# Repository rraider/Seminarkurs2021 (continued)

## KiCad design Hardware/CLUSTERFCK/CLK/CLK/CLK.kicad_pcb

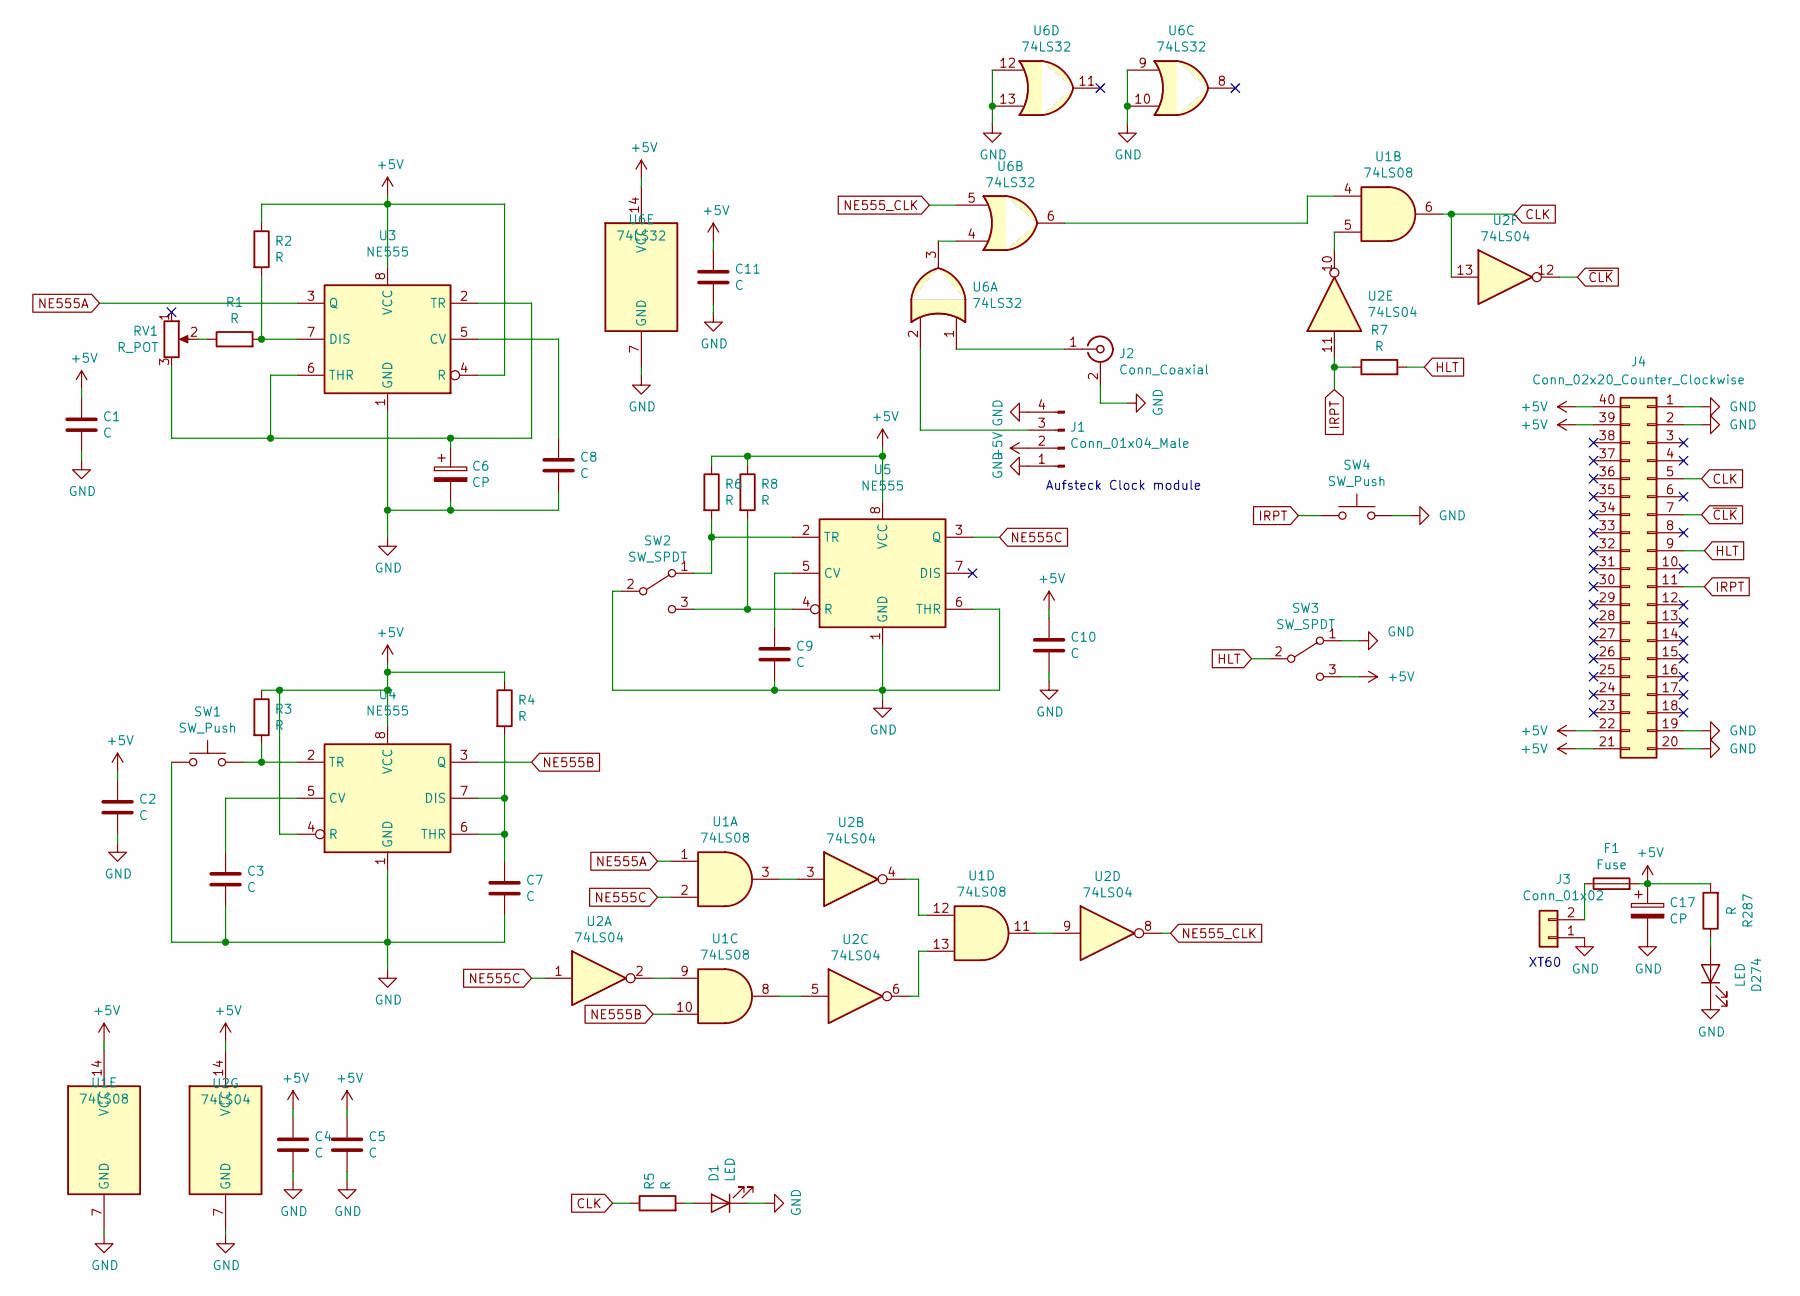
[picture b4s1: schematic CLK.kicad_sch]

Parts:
C1, C2, C3, C4, C5, C7, C8, C9, C10, C11: C; C_0805_2012Metric_Pad1.15x1.40mm_HandSolder
C6, C17: CP; C_0805_2012Metric_Pad1.15x1.40mm_HandSolder
D1, D274: LED; LED_D5.0mm
F1: Fuse; Fuseholder_Cylinder-5x20mm_Stelvio-Kontek_PTF78_Horizontal_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
J1: Conn_01x04_Male; PinHeader_1x04_P2.54mm_Vertical
J2: Conn_Coaxial; SMA_Amphenol_901-144_Vertical
J3: Conn_01x02; AMASS_XT30U-F_1x02_P5.0mm_Vertical
J4: Conn_02x20_Counter_Clockwise; PinSocket_2x20_P2.54mm_Horizontal
R1, R2, R3, R4, R5, R6, R7, R8, R287: R; R_0805_2012Metric_Pad1.15x1.40mm_HandSolder
RV1: R_POT; Potentiometer_ACP_CA6-H2,5_Horizontal
SW1, SW4: SW_Push; Push_E-Switch_KS01Q01
SW2, SW3: SW_SPDT; SW_CuK_JS202011CQN_DPDT_Straight
U1: 74LS08; SOIC-14_3.9x8.7mm_P1.27mm
U2: 74LS04; SOIC-14_3.9x8.7mm_P1.27mm
U3, U4, U5: NE555; DIP-8_W10.16mm
U6: 74LS32; SOIC-14_3.9x8.7mm_P1.27mm

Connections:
+5V: C1.1, C2.1, C4.1, C5.1, C10.1, C11.1, C17.1, F1.2, J1.2, J4.21, J4.22, J4.39, J4.40, R2.1, R3.1, R4.1, R6.1, R8.1, R287.2, SW3.3 (C), U1.14 (VCC), U2.14 (VCC), U3.4 (R), U3.8 (VCC), U4.4 (R), U4.8 (VCC), U5.8 (VCC), U6.14 (VCC)
CLK: J4.5, R5.1, U1.6, U2.13
GND: C1.2, C2.2, C3.2, C4.2, C5.2, C6.2, C7.2, C8.2, C9.2, C10.2, C11.2, C17.2, D1.1 (K), D274.1 (K), J1.1, J1.4, J2.2 (Ext), J3.1, J4.1, J4.2, J4.19, J4.20, SW1.1, SW2.2 (B), SW3.1 (A), SW4.2, U1.7 (GND), U2.7 (GND), U3.1 (GND), U4.1 (GND), U5.1 (GND), U5.6 (THR), U6.7 (GND), U6.9, U6.10, U6.12, U6.13
HLT: J4.9, R7.2, SW3.2 (B)
IRPT: J4.11, R7.1, SW4.1, U2.11
NE555A: U1.1, U3.3 (Q)
NE555B: U1.10, U4.3 (Q)
NE555C: U1.2, U2.1, U5.3 (Q)
NE555_CLK: U2.8, U6.5
unnamed: C3.1, U4.5 (CV)
unnamed: C6.1, RV1.3, U3.2 (TR), U3.6 (THR)
unnamed: C7.1, R4.2, U4.6 (THR), U4.7 (DIS)
unnamed: C8.1, U3.5 (CV)
unnamed: C9.1, U5.5 (CV)
unnamed: D1.2 (A), R5.2
unnamed: D274.2 (A), R287.1
unnamed: F1.1, J3.2
unnamed: J1.3, U6.2
unnamed: J2.1 (In), U6.1
unnamed: R1.1, RV1.2
unnamed: R1.2, R2.2, U3.7 (DIS)
unnamed: R3.2, SW1.2, U4.2 (TR)
unnamed: R6.2, SW2.1 (A), U5.2 (TR)
unnamed: R8.2, SW2.3 (C), U5.4 (R)
unnamed: U1.3, U2.3
unnamed: U1.4, U6.6
unnamed: U1.5, U2.10
unnamed: U1.8, U2.5
unnamed: U1.9, U2.2
unnamed: U1.11, U2.9
unnamed: U1.12, U2.4
unnamed: U1.13, U2.6
unnamed: U6.3, U6.4
no_connect_35: J4.10
no_connect_36: J4.12
no_connect_37: J4.13
no_connect_38: J4.14
no_connect_39: J4.15
no_connect_40: J4.16
no_connect_41: J4.17
no_connect_42: J4.18
no_connect_43: J4.23
no_connect_44: J4.24
no_connect_45: J4.25
no_connect_46: J4.26
no_connect_47: J4.27
no_connect_48: J4.28
no_connect_49: J4.29
no_connect_50: J4.3
no_connect_51: J4.30
no_connect_52: J4.31
no_connect_53: J4.32
no_connect_54: J4.33
no_connect_55: J4.34
no_connect_56: J4.35
no_connect_57: J4.36
no_connect_58: J4.37
no_connect_59: J4.38
no_connect_60: J4.4
no_connect_61: J4.6
no_connect_62: J4.8
no_connect_63: RV1.1
no_connect_64: U5.7 (DIS)
no_connect_65: U6.11
no_connect_66: U6.8
~CLK: J4.7, U2.12

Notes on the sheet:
Aufsteck Clock module
XT60

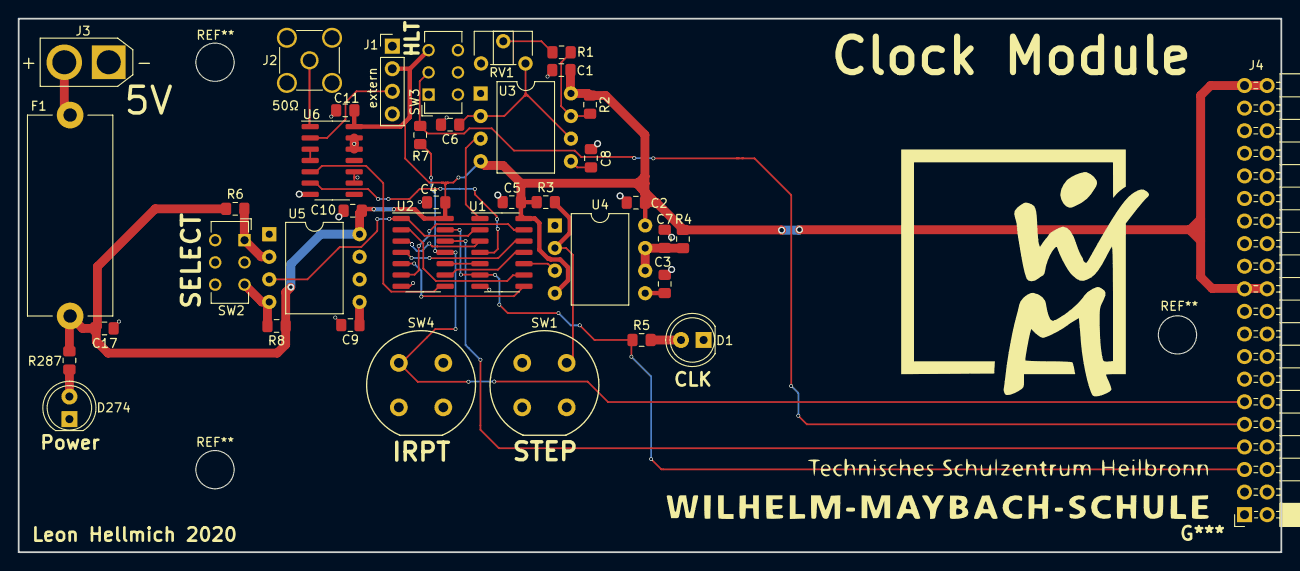
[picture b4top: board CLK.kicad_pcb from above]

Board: 2 copper layers, 142.0 x 60.0 mm, 39 parts (0 on the bottom side), 34 nets.

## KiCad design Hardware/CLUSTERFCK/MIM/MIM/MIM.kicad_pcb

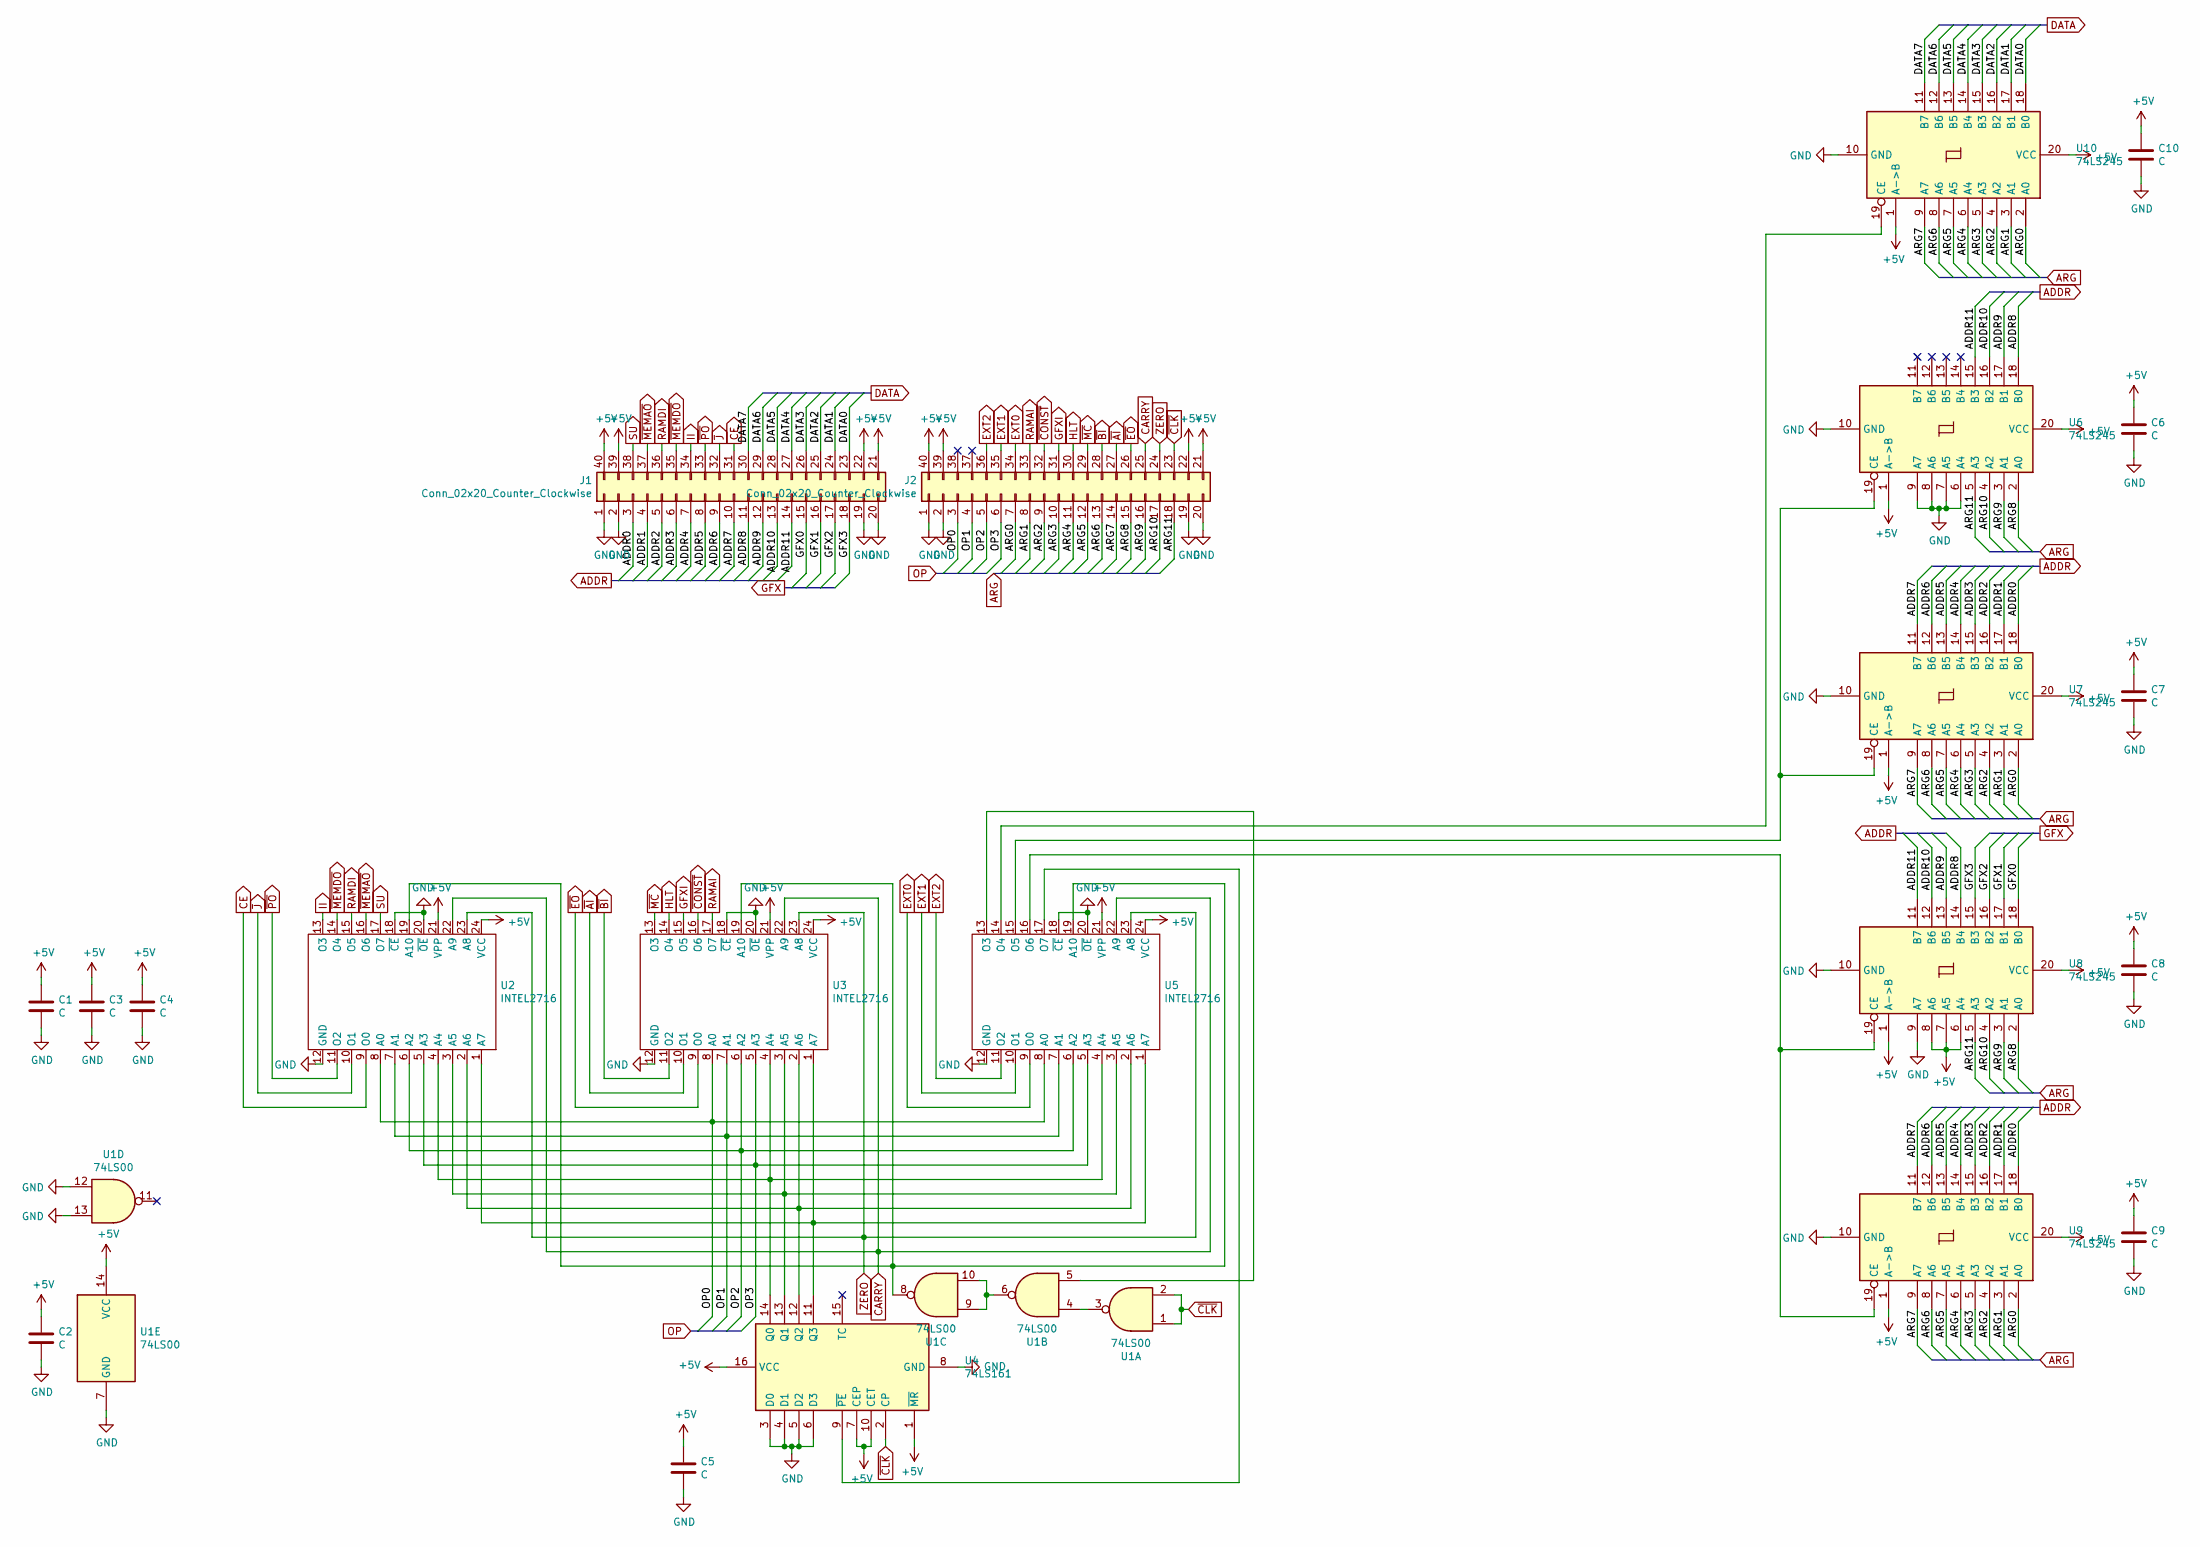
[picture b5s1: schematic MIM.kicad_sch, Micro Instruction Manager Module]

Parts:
C1, C2, C3, C4, C5, C6, C7, C8, C9, C10: C; C_0805_2012Metric_Pad1.15x1.40mm_HandSolder
J1, J2: Conn_02x20_Counter_Clockwise; PinSocket_2x20_P2.54mm_Horizontal
U1: 74LS00; SOIC-14_3.9x8.7mm_P1.27mm
U2, U3, U5: INTEL2716; DIP-24_W15.24mm_Socket_LongPads
U4: 74LS161; SOIC-16_3.9x9.9mm_P1.27mm
U6, U7, U8, U9, U10: 74LS245; SOIC-20W_7.5x12.8mm_P1.27mm

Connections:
+5V: C1.1, C2.1, C3.1, C4.1, C5.1, C6.1, C7.1, C8.1, C9.1, C10.1, J1.21, J1.22, J1.39, J1.40, J2.21, J2.22, J2.39, J2.40, U1.14 (VCC), U2.21 (VPP), U2.24 (VCC), U3.21 (VPP), U3.24 (VCC), U4.1 (~MR), U4.7 (CEP), U4.10 (CET), U4.16 (VCC), U5.21 (VPP), U5.24 (VCC), U6.1 (A->B), U6.20 (VCC), U7.1 (A->B), U7.20 (VCC), U8.1 (A->B), U8.6 (A4), U8.7 (A5), U8.8 (A6), U8.20 (VCC), U9.1 (A->B), U9.20 (VCC), U10.1 (A->B), U10.20 (VCC)
/ADDR0: J1.3, U7.18 (B0), U9.18 (B0)
/ADDR1: J1.4, U7.17 (B1), U9.17 (B1)
/ADDR2: J1.5, U7.16 (B2), U9.16 (B2)
/ADDR3: J1.6, U7.15 (B3), U9.15 (B3)
/ADDR4: J1.7, U7.14 (B4), U9.14 (B4)
/ADDR5: J1.8, U7.13 (B5), U9.13 (B5)
/ADDR6: J1.9, U7.12 (B6), U9.12 (B6)
/ADDR7: J1.10, U7.11 (B7), U9.11 (B7)
/ADDR8: J1.11, U6.18 (B0), U8.14 (B4)
/ADDR9: J1.12, U6.17 (B1), U8.13 (B5)
/ADDR10: J1.13, U6.16 (B2), U8.12 (B6)
/ADDR11: J1.14, U6.15 (B3), U8.11 (B7)
/ARG0: J2.7, U7.2 (A0), U9.2 (A0), U10.2 (A0)
/ARG1: J2.8, U7.3 (A1), U9.3 (A1), U10.3 (A1)
/ARG2: J2.9, U7.4 (A2), U9.4 (A2), U10.4 (A2)
/ARG3: J2.10, U7.5 (A3), U9.5 (A3), U10.5 (A3)
/ARG4: J2.11, U7.6 (A4), U9.6 (A4), U10.6 (A4)
/ARG5: J2.12, U7.7 (A5), U9.7 (A5), U10.7 (A5)
/ARG6: J2.13, U7.8 (A6), U9.8 (A6), U10.8 (A6)
/ARG7: J2.14, U7.9 (A7), U9.9 (A7), U10.9 (A7)
/ARG8: J2.15, U6.2 (A0), U8.2 (A0)
/ARG9: J2.16, U6.3 (A1), U8.3 (A1)
/ARG10: J2.17, U6.4 (A2), U8.4 (A2)
/ARG11: J2.18, U6.5 (A3), U8.5 (A3)
/DATA0: J1.23, U10.18 (B0)
/DATA1: J1.24, U10.17 (B1)
/DATA2: J1.25, U10.16 (B2)
/DATA3: J1.26, U10.15 (B3)
/DATA4: J1.27, U10.14 (B4)
/DATA5: J1.28, U10.13 (B5)
/DATA6: J1.29, U10.12 (B6)
/DATA7: J1.30, U10.11 (B7)
/GFX0: J1.15, U8.18 (B0)
/GFX1: J1.16, U8.17 (B1)
/GFX2: J1.17, U8.16 (B2)
/GFX3: J1.18, U8.15 (B3)
/OP0: J2.3, U2.8 (A0), U3.8 (A0), U5.8 (A0)
/OP1: J2.4, U2.7 (A1), U3.7 (A1), U5.7 (A1)
/OP2: J2.5, U2.6 (A2), U3.6 (A2), U5.6 (A2)
/OP3: J2.6, U2.5 (A3), U3.5 (A3), U5.5 (A3)
AI: J2.27, U3.10 (O1)
BI: J2.28, U3.11 (O2)
CARRY: J2.25, U2.22 (A9), U3.22 (A9), U5.22 (A9)
CE: J1.31, U2.9 (O0)
CONST: J2.32, U3.16 (O6)
EO: J2.26, U3.9 (O0)
EXT0: J2.34, U5.9 (O0)
EXT1: J2.35, U5.10 (O1)
EXT2: J2.36, U5.11 (O2)
GFXI: J2.31, U3.15 (O5)
GND: C1.2, C2.2, C3.2, C4.2, C5.2, C6.2, C7.2, C8.2, C9.2, C10.2, J1.1, J1.2, J1.19, J1.20, J2.1, J2.2, J2.19, J2.20, U1.7 (GND), U1.12, U1.13, U2.12 (GND), U2.18 (~CE), U2.20 (~OE), U3.12 (GND), U3.18 (~CE), U3.20 (~OE), U4.3 (D0), U4.4 (D1), U4.5 (D2), U4.6 (D3), U4.8 (GND), U5.12 (GND), U5.18 (~CE), U5.20 (~OE), U6.6 (A4), U6.7 (A5), U6.8 (A6), U6.9 (A7), U6.10 (GND), U7.10 (GND), U8.9 (A7), U8.10 (GND), U9.10 (GND), U10.10 (GND)
HLT: J2.30, U3.14 (O4)
II: J1.34, U2.13 (O3)
J: J1.32, U2.10 (O1)
MC: J2.29, U3.13 (O3)
MEMAO: J1.37, U2.16 (O6)
MEMDO: J1.35, U2.14 (O4)
unnamed: U1.3, U1.4
unnamed: U1.5, U5.13 (O3)
unnamed: U1.8, U2.19 (A10), U3.19 (A10), U5.19 (A10)
unnamed: U1.6, U1.9, U1.10
unnamed: U2.1 (A7), U3.1 (A7), U4.11 (Q3), U5.1 (A7)
unnamed: U2.2 (A6), U3.2 (A6), U4.12 (Q2), U5.2 (A6)
unnamed: U2.3 (A5), U3.3 (A5), U4.13 (Q1), U5.3 (A5)
unnamed: U2.4 (A4), U3.4 (A4), U4.14 (Q0), U5.4 (A4)
unnamed: U4.9 (~PE), U5.17 (O7)
unnamed: U5.15 (O5), U6.19 (CE), U7.19 (CE)
unnamed: U5.16 (O6), U8.19 (CE), U9.19 (CE)
unnamed: U5.14 (O4), U10.19 (CE)
PO: J1.33, U2.11 (O2)
RAMAI: J2.33, U3.17 (O7)
RAMDI: J1.36, U2.15 (O5)
SU: J1.38, U2.17 (O7)
ZERO: J2.24, U2.23 (A8), U3.23 (A8), U5.23 (A8)
~CLK: J2.23, U1.1, U1.2, U4.2 (CP)

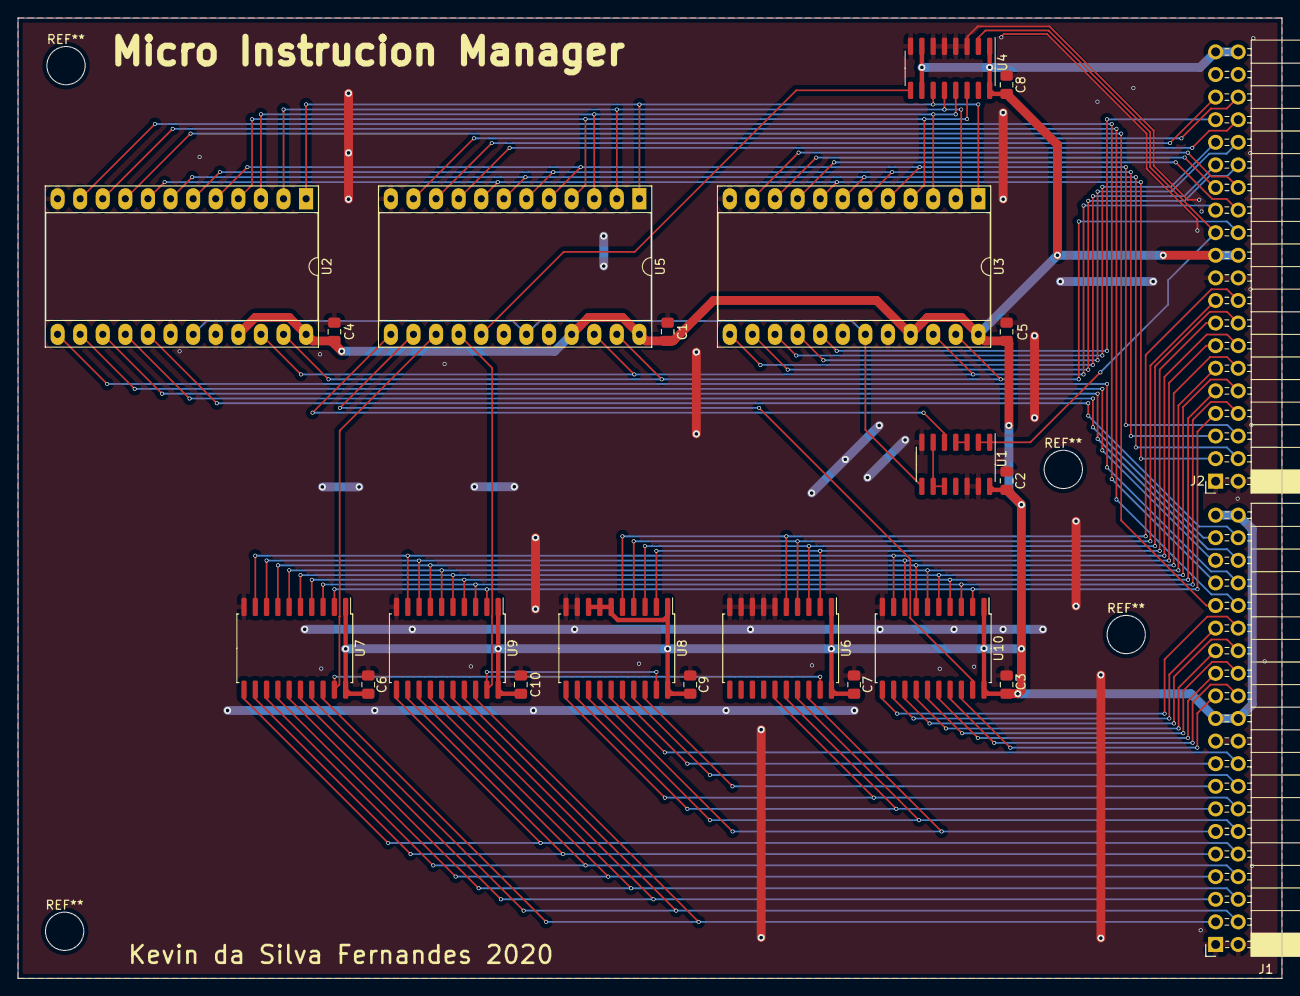
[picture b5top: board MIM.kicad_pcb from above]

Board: 2 copper layers, 142.1 x 108.0 mm, 22 parts (0 on the bottom side), 76 nets.

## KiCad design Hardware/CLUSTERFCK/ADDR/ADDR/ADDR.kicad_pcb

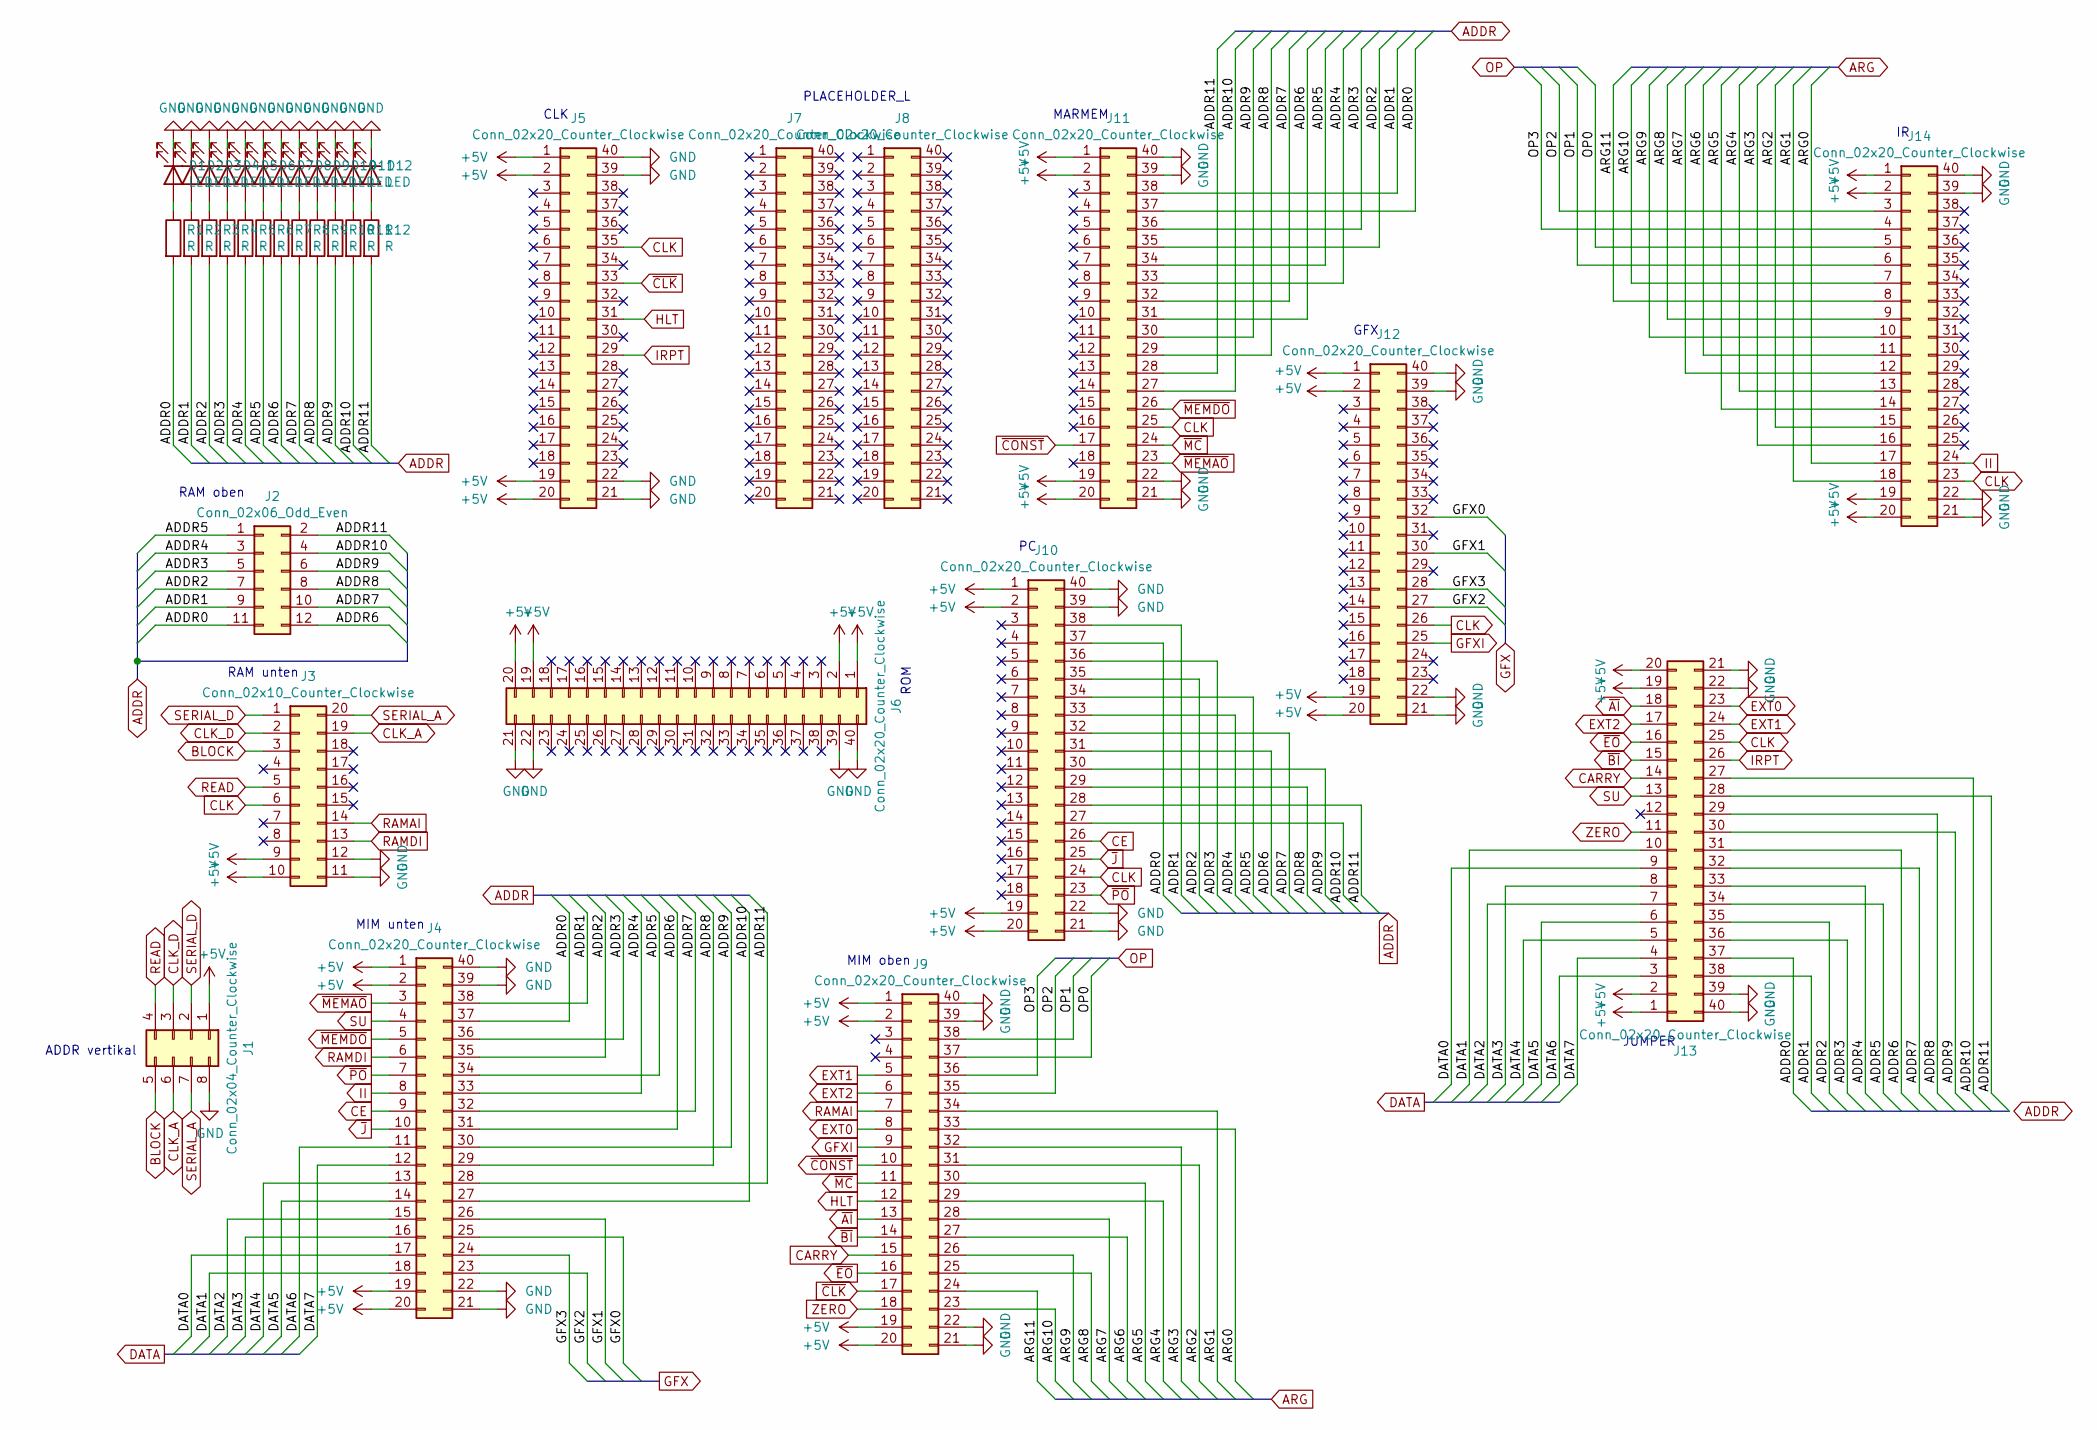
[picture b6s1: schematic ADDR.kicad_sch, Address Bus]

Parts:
D1, D2, D3, D4, D5, D6, D7, D8, D9, D10, D11, D12: LED; LED_D5.0mm
J1: Conn_02x04_Counter_Clockwise; PinHeader_2x04_P2.54mm_Vertical
J2: Conn_02x06_Odd_Even; PinHeader_2x06_P2.54mm_Horizontal
J3: Conn_02x10_Counter_Clockwise; PinHeader_2x10_P2.54mm_Horizontal
J4, J5, J6, J7, J8, J9, J10, J11, J12, J14: Conn_02x20_Counter_Clockwise; PinSocket_2x20_P2.54mm_Horizontal
J13: Conn_02x20_Counter_Clockwise; PinHeader_2x20_P2.54mm_Horizontal
R1, R2, R3, R4, R5, R6, R7, R8, R9, R10, R11, R12: R; R_0805_2012Metric_Pad1.15x1.40mm_HandSolder

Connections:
+5V: J1.1, J3.9, J3.10, J4.1, J4.2, J4.19, J4.20, J5.1, J5.2, J5.19, J5.20, J6.1, J6.2, J6.19, J6.20, J9.1, J9.2, J9.19, J9.20, J10.1, J10.2, J10.19, J10.20, J11.1, J11.2, J11.19, J11.20, J12.1, J12.2, J12.19, J12.20, J13.1, J13.2, J13.19, J13.20, J14.1, J14.2, J14.19, J14.20
/ADDR0: J2.11, J4.37, J10.37, J11.37, J13.37, R1.2
/ADDR1: J2.9, J4.38, J10.38, J11.38, J13.38, R2.2
/ADDR2: J2.7, J4.35, J10.35, J11.35, J13.35, R3.2
/ADDR3: J2.5, J4.36, J10.36, J11.36, J13.36, R4.2
/ADDR4: J2.3, J4.33, J10.33, J11.33, J13.33, R5.2
/ADDR5: J2.1, J4.34, J10.34, J11.34, J13.34, R6.2
/ADDR6: J2.12, J4.31, J10.31, J11.31, J13.31, R7.2
/ADDR7: J2.10, J4.32, J10.32, J11.32, J13.32, R8.2
/ADDR8: J2.8, J4.29, J10.29, J11.29, J13.29, R9.2
/ADDR9: J2.6, J4.30, J10.30, J11.30, J13.30, R10.2
/ADDR10: J2.4, J4.27, J10.27, J11.27, J13.27, R11.2
/ADDR11: J2.2, J4.28, J10.28, J11.28, J13.28, R12.2
/ARG0: J9.33, J14.17
/ARG1: J9.34, J14.18
/ARG2: J9.31, J14.15
/ARG3: J9.32, J14.16
/ARG4: J9.29, J14.13
/ARG5: J9.30, J14.14
/ARG6: J9.27, J14.11
/ARG7: J9.28, J14.12
/ARG8: J9.25, J14.9
/ARG9: J9.26, J14.10
/ARG10: J9.23, J14.7
/ARG11: J9.24, J14.8
/DATA0: J4.17, J13.9
/DATA1: J4.18, J13.10
/DATA2: J4.15, J13.7
/DATA3: J4.16, J13.8
/DATA4: J4.13, J13.5
/DATA5: J4.14, J13.6
/DATA6: J4.11, J13.3
/DATA7: J4.12, J13.4
/GFX0: J4.25, J12.32
/GFX1: J4.26, J12.30
/GFX2: J4.23, J12.27
/GFX3: J4.24, J12.28
/OP0: J9.37, J14.5
/OP1: J9.38, J14.6
/OP2: J9.35, J14.3
/OP3: J9.36, J14.4
BLOCK: J1.5, J3.3
CARRY: J9.15, J13.14
CE: J4.9, J10.26
CLK: J3.6, J5.35, J10.24, J11.25, J12.26, J13.25, J14.23
CLK_A: J1.6, J3.19
CLK_D: J1.3, J3.2
EXT0: J9.8, J13.23
EXT1: J9.5, J13.24
EXT2: J9.6, J13.17
GFXI: J9.9, J12.25
GND: D1.1 (K), D2.1 (K), D3.1 (K), D4.1 (K), D5.1 (K), D6.1 (K), D7.1 (K), D8.1 (K), D9.1 (K), D10.1 (K), D11.1 (K), D12.1 (K), J1.8, J3.11, J3.12, J4.21, J4.22, J4.39, J4.40, J5.21, J5.22, J5.39, J5.40, J6.21, J6.22, J6.39, J6.40, J9.21, J9.22, J9.39, J9.40, J10.21, J10.22, J10.39, J10.40, J11.21, J11.22, J11.39, J11.40, J12.21, J12.22, J12.39, J12.40, J13.21, J13.22, J13.39, J13.40, J14.21, J14.22, J14.39, J14.40
HLT: J5.31, J9.12
II: J4.8, J14.24
IRPT: J5.29, J13.26
unnamed: D6.2 (A), R6.1
unnamed: D1.2 (A), R1.1
unnamed: D2.2 (A), R2.1
unnamed: D3.2 (A), R3.1
unnamed: D4.2 (A), R4.1
unnamed: D5.2 (A), R5.1
unnamed: D7.2 (A), R7.1
unnamed: D8.2 (A), R8.1
unnamed: D9.2 (A), R9.1
unnamed: D10.2 (A), R10.1
unnamed: D11.2 (A), R11.1
unnamed: D12.2 (A), R12.1
RAMAI: J3.14, J9.7
RAMDI: J3.13, J4.6
READ: J1.4, J3.5
SERIAL_A: J1.7, J3.20
SERIAL_D: J1.2, J3.1
SU: J4.4, J13.13
ZERO: J9.18, J13.11
~AI: J9.13, J13.18
~BI: J9.14, J13.15
~CLK: J5.33, J9.17
~CONST: J9.10, J11.17
~EO: J9.16, J13.16
~J: J4.10, J10.25
~MC: J9.11, J11.24
~MEMAO: J4.3, J11.23
~MEMDO: J4.5, J11.26
~PO: J4.7, J10.23

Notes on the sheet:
ADDR vertikal
RAM oben
RAM unten
MIM unten
CLK
PLACEHOLDER_L
ROM
MIM oben
MARMEM
GFX
JUMPER

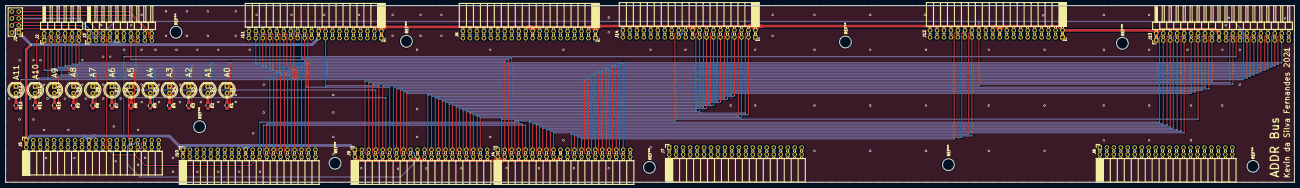
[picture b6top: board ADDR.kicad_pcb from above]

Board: 2 copper layers, 469.5 x 64.3 mm, 38 parts (0 on the bottom side), 84 nets.

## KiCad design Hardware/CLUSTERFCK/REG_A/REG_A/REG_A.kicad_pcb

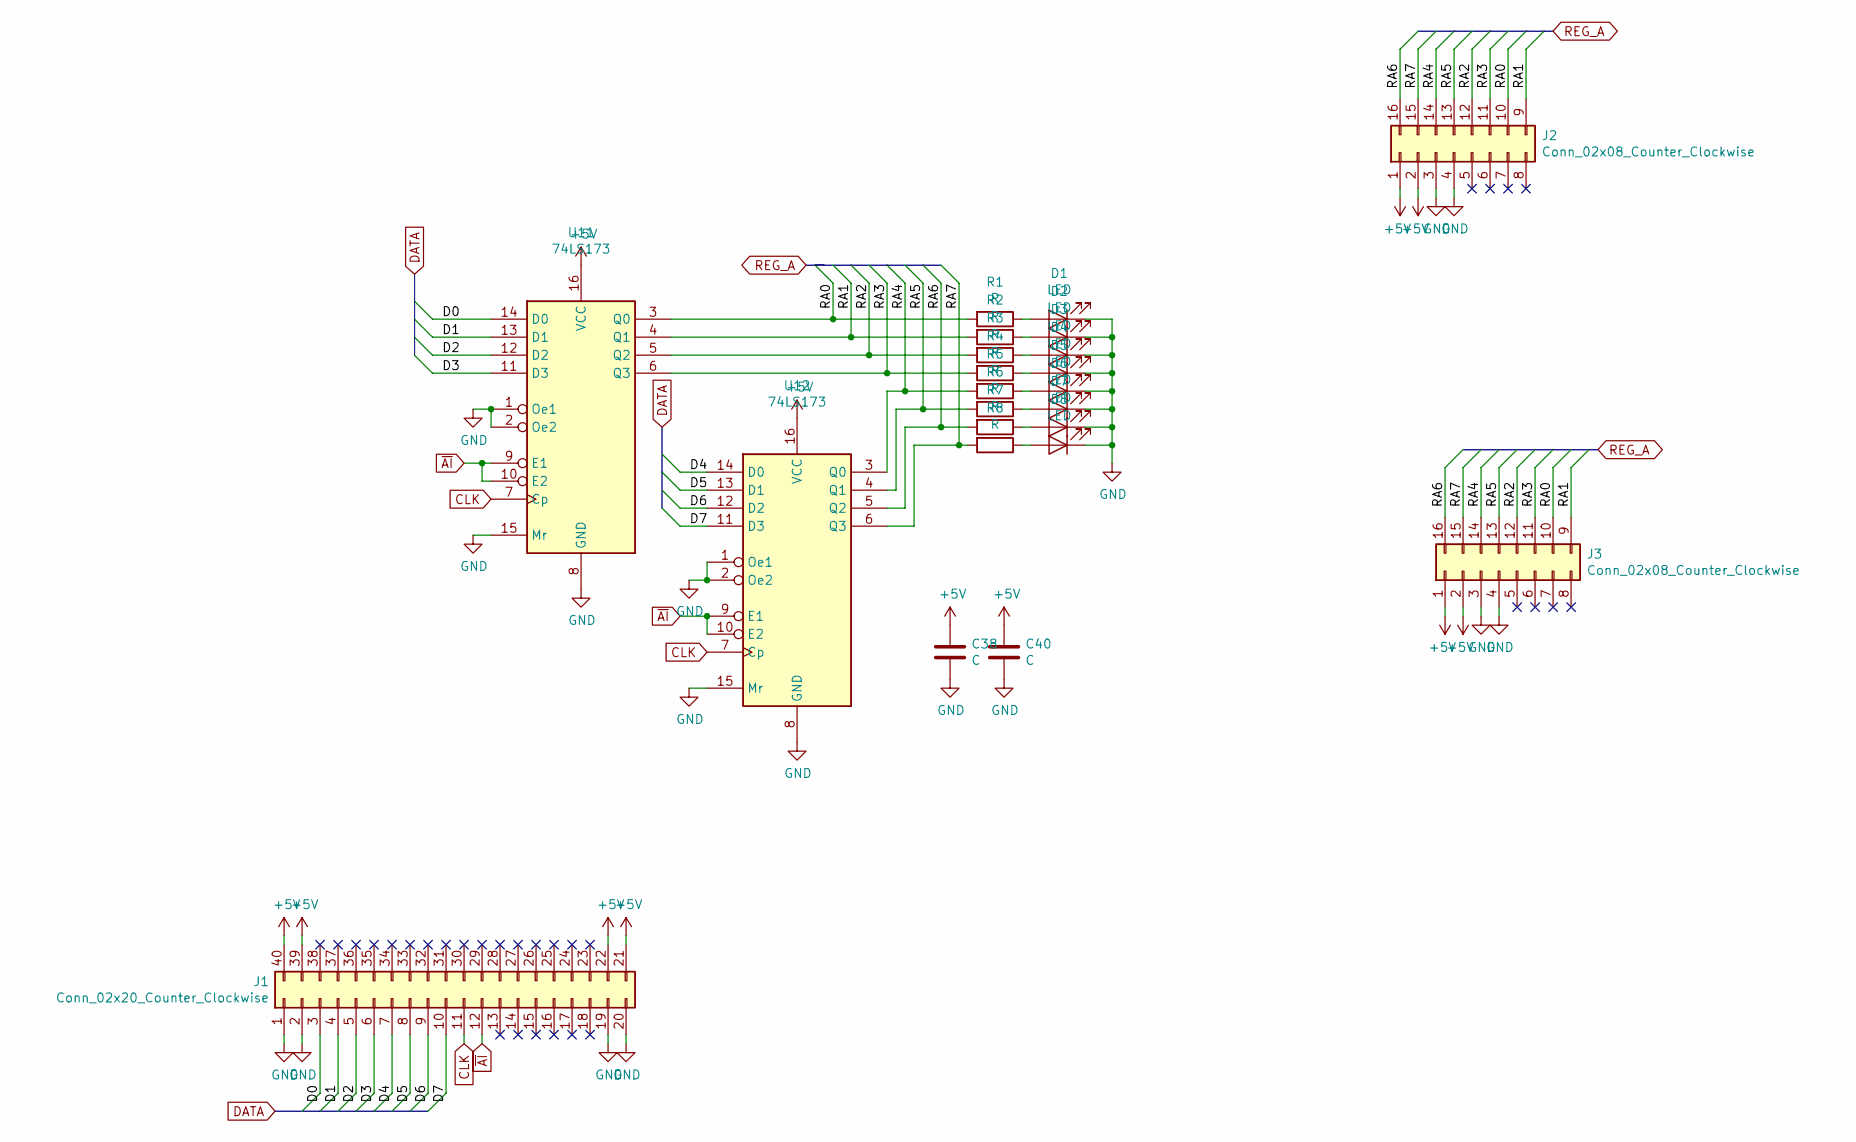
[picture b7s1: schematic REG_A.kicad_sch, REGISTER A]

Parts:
C38, C40: C; C_0805_2012Metric_Pad1.15x1.40mm_HandSolder
D1, D2, D3, D4, D5, D6, D7, D8: LED; LED_D5.0mm
J1: Conn_02x20_Counter_Clockwise; PinHeader_2x20_P2.54mm_Horizontal
J2, J3: Conn_02x08_Counter_Clockwise; PinHeader_2x08_P2.54mm_Horizontal
R1, R2, R3, R4, R5, R6, R7, R8: R; R_0805_2012Metric_Pad1.15x1.40mm_HandSolder
U11, U12: 74LS173; SOIC-16W_7.5x10.3mm_P1.27mm

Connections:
+5V: C38.1, C40.1, J1.21, J1.22, J1.39, J1.40, J2.1, J2.2, J3.1, J3.2, U11.16 (VCC), U12.16 (VCC)
/D0: J1.3, U11.14 (D0)
/D1: J1.4, U11.13 (D1)
/D2: J1.5, U11.12 (D2)
/D3: J1.6, U11.11 (D3)
/D4: J1.7, U12.14 (D0)
/D5: J1.8, U12.13 (D1)
/D6: J1.9, U12.12 (D2)
/D7: J1.10, U12.11 (D3)
/RA0: J2.10, J3.10, R1.2, U11.3 (Q0)
/RA1: J2.9, J3.9, R2.2, U11.4 (Q1)
/RA2: J2.12, J3.12, R3.2, U11.5 (Q2)
/RA3: J2.11, J3.11, R4.2, U11.6 (Q3)
/RA4: J2.14, J3.14, R5.2, U12.3 (Q0)
/RA5: J2.13, J3.13, R6.2, U12.4 (Q1)
/RA6: J2.16, J3.16, R7.2, U12.5 (Q2)
/RA7: J2.15, J3.15, R8.2, U12.6 (Q3)
CLK: J1.11, U11.7 (Cp), U12.7 (Cp)
GND: C38.2, C40.2, D1.1 (K), D2.1 (K), D3.1 (K), D4.1 (K), D5.1 (K), D6.1 (K), D7.1 (K), D8.1 (K), J1.1, J1.2, J1.19, J1.20, J2.3, J2.4, J3.3, J3.4, U11.1 (Oe1), U11.2 (Oe2), U11.8 (GND), U11.15 (Mr), U12.1 (Oe1), U12.2 (Oe2), U12.8 (GND), U12.15 (Mr)
unnamed: D1.2 (A), R1.1
unnamed: D2.2 (A), R2.1
unnamed: D3.2 (A), R3.1
unnamed: D4.2 (A), R4.1
unnamed: D5.2 (A), R5.1
unnamed: D6.2 (A), R6.1
unnamed: D7.2 (A), R7.1
unnamed: D8.2 (A), R8.1
~AI: J1.12, U11.9 (E1), U11.10 (E2), U12.9 (E1), U12.10 (E2)

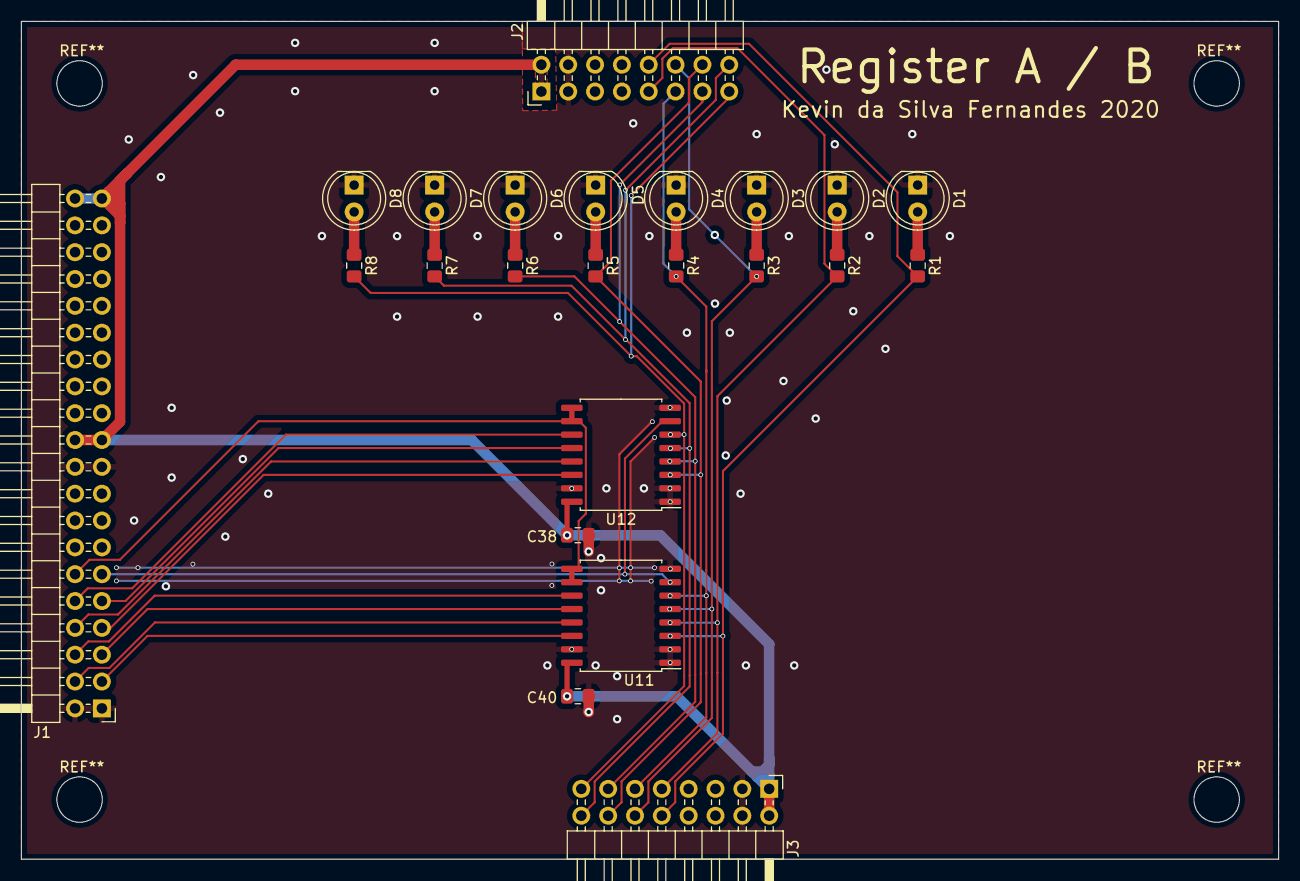
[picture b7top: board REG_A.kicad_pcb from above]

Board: 2 copper layers, 119.0 x 79.3 mm, 23 parts (0 on the bottom side), 28 nets.
